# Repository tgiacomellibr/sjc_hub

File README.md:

# SJC Network Hub

- Power input filter
- RS-485 Network Hub
- Endstop connections

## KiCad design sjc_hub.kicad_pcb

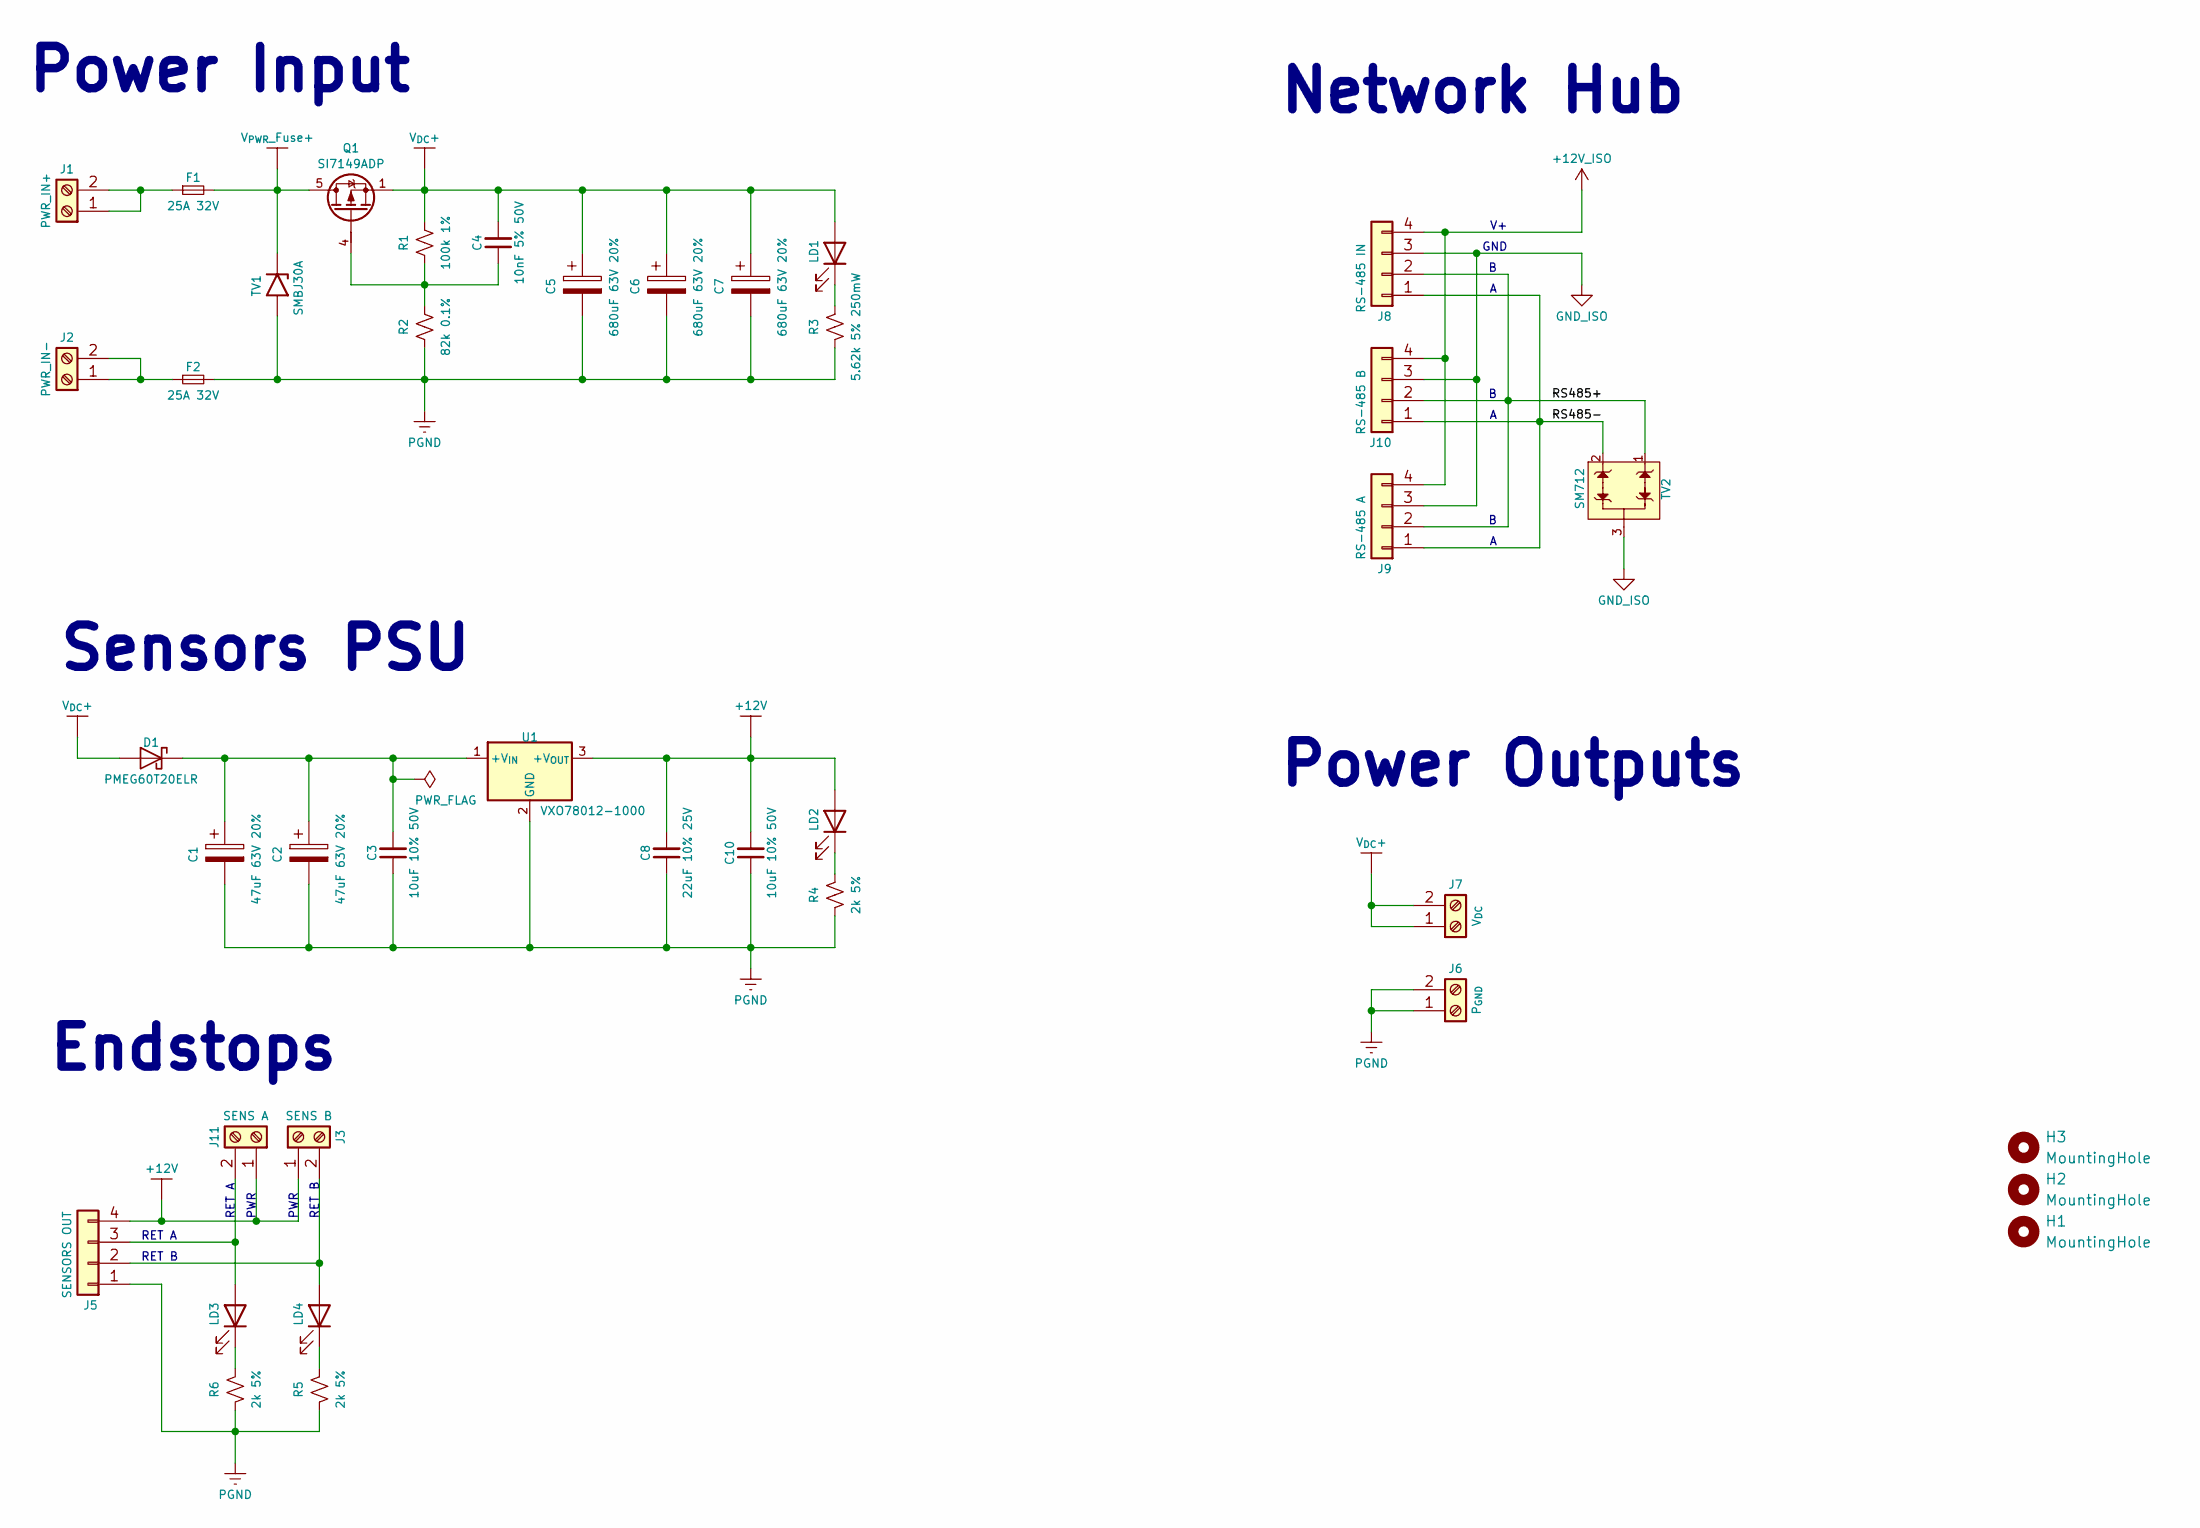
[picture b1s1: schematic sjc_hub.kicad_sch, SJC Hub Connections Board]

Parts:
C1, C2: 47uF 63V 20%; CP_Elec_8x10.5; JLCPCB Part # C116428
C3, C10: 10uF 10% 50V; C_1206_3216Metric; JLCPCB Part # C13585
C4: 10nF 5% 50V; C_0603_1608Metric; JLCPCB Part # C389113
C5, C6, C7: 680uF 63V 20%; CP_Elec_18x17.5; JLCPCB Part # C249956
C8: 22uF 10% 25V; C_1206_3216Metric; JLCPCB Part # C105213
D1: PMEG60T20ELR; D_SOD-123F; JLCPCB Part # C552947
F1, F2: 25A 32V; Fuse_1206_3216Metric_Pad1.42x1.75mm_HandSolder; JLCPCB Part # C2925001
H1, H2, H3: MountingHole; MountingHole_4.3mm_M4_DIN965
J1: PWR_IN+; TerminalBlock_Phoenix_MKDS-3-2-5.08_1x02_P5.08mm_Horizontal; JLCPCB Part # C8465
J2: PWR_IN-; TerminalBlock_Phoenix_MKDS-3-2-5.08_1x02_P5.08mm_Horizontal; JLCPCB Part # C8465
J3: SENS B; TerminalBlock_Phoenix_MKDS-3-2-5.08_1x02_P5.08mm_Horizontal; JLCPCB Part # C8465
J5: SENSORS OUT; Molex_KK-396_A-41791-0004_1x04_P3.96mm_Vertical
J6: P_{GND}; TerminalBlock_Phoenix_MKDS-3-2-5.08_1x02_P5.08mm_Horizontal; JLCPCB Part # C8465
J7: V_{DC}; TerminalBlock_Phoenix_MKDS-3-2-5.08_1x02_P5.08mm_Horizontal; JLCPCB Part # C8465
J8: RS-485 IN; Molex_KK-396_A-41791-0004_1x04_P3.96mm_Vertical
J9: RS-485 A; Molex_KK-396_A-41791-0004_1x04_P3.96mm_Vertical
J10: RS-485 B; Molex_KK-396_A-41791-0004_1x04_P3.96mm_Vertical
J11: SENS A; TerminalBlock_Phoenix_MKDS-3-2-5.08_1x02_P5.08mm_Horizontal; JLCPCB Part # C8465
LD1, LD2, LD3, LD4: 1.8V @ 5mA; LED_0603_1608Metric_Pad1.05x0.95mm_HandSolder; JLCPCB Part # C165982
Q1: SI7149ADP; PowerPAK_SO-8_Single; JLCPCB Part # C554002
R1: 100k 1%; R_0603_1608Metric; JLCPCB Part # C14675
R2: 82k 0.1%; R_0603_1608Metric; JLCPCB Part # C728598
R3: 5.62k 5% 250mW; R_0805_2012Metric_Pad1.20x1.40mm_HandSolder; JLCPCB Part # C425493
R4, R5, R6: 2k 5%; R_0603_1608Metric; JLCPCB Part # C103396
TV1: SMBJ30A; D_SMB_Handsoldering; JLCPCB Part # C83851
TV2: SM712; SOT-23-3; JLCPCB Part # C293966
U1: VXO78012-1000; CONV_VXO78012-1000; Mouser # 490-VXO7812-1000

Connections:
+12V: C8.2, C10.2, J3.1, J5.4, J11.1, LD2.2 (A), U1.3 (+V_{OUT})
+12V_ISO: J8.4, J9.4, J10.4
/RS485+: J8.2, J9.2, J10.2, TV2.1
/RS485-: J8.1, J9.1, J10.1, TV2.2
GND_ISO: J8.3, J9.3, J10.3, TV2.3
unnamed: C1.1, C2.1, C3.2, D1.1 (K), U1.1 (+V_{IN})
unnamed: F1.1, J1.1, J1.2
unnamed: F2.1, J2.1, J2.2
unnamed: J3.2, J5.2, LD4.2 (A)
unnamed: J5.3, J11.2, LD3.2 (A)
unnamed: LD1.1 (K), R3.1
unnamed: LD2.1 (K), R4.1
unnamed: LD3.1 (K), R6.1
unnamed: LD4.1 (K), R5.1
unnamed 14: C4.1, Q1.4 (G), R1.1, R2.2; also elsewhere on the board
PGND: C1.2, C2.2, C3.1, C5.2, C6.2, C7.2, C8.1, C10.1, F2.2, J5.1, J6.1, J6.2, R2.1, R3.2, R4.2, R5.2, R6.2, TV1.2 (A), U1.2 (GND); also elsewhere on the board
V_{DC}+: C4.2, C5.1, C6.1, C7.1, D1.2 (A), J7.1, J7.2, LD1.2 (A), Q1.1 (S), Q1.2 (S), Q1.3 (S), R1.2; also elsewhere on the board
V_{PWR}_Fuse+: F1.2, Q1.5 (D), TV1.1 (K)

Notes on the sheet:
Power Input
RET A
PWR
RET B
Sensors PSU
Network Hub
Endstops
Power Outputs
GND

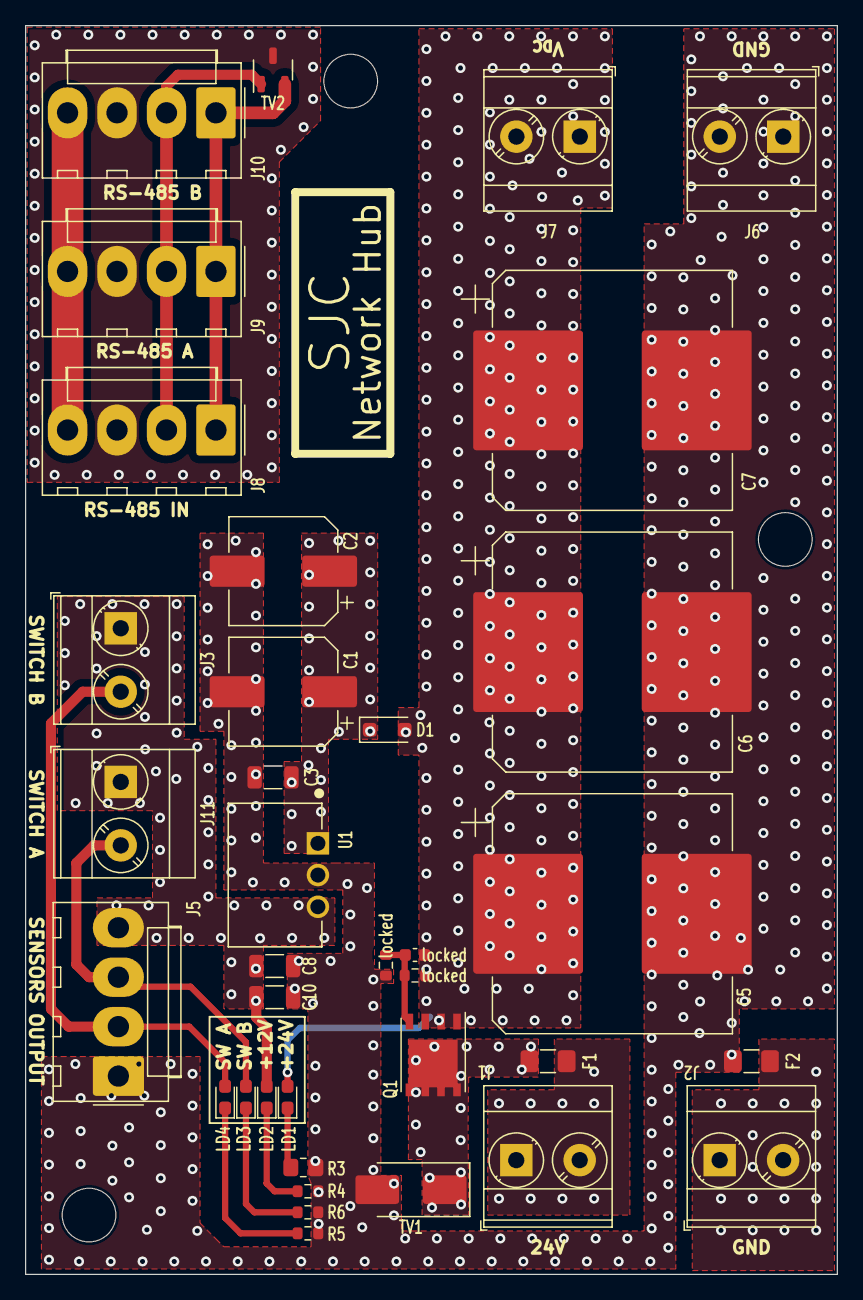
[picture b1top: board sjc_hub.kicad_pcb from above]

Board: 2 copper layers, 65.0 x 100.0 mm, 39 parts (0 on the bottom side), 18 nets.

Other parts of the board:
locked: 10nF 5% 50V; C_0603_1608Metric
locked#2: 82k 0.1%; R_0603_1608Metric
locked#3: 100k 1%; R_0603_1608Metric

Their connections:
unnamed 14: locked.1, locked#2.2, locked#3.1; also elsewhere on the board
PGND: locked#2.1; also elsewhere on the board
V_{DC}+: locked.2, locked#3.2; also elsewhere on the board

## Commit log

2023-12-08 pcb updates
